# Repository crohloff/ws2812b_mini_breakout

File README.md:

# ws2812b-mini breakout
in-pcb placed ws2812b-mini

## dimensions
- 30mm x 25mm

## features
- 9 LEDs
- 3.3V - 5V level shifter
- in-pcb placed ws2812b-mini

## board front

## board back

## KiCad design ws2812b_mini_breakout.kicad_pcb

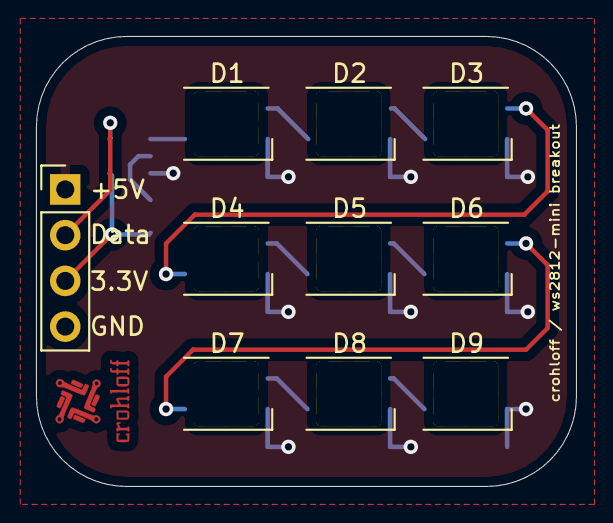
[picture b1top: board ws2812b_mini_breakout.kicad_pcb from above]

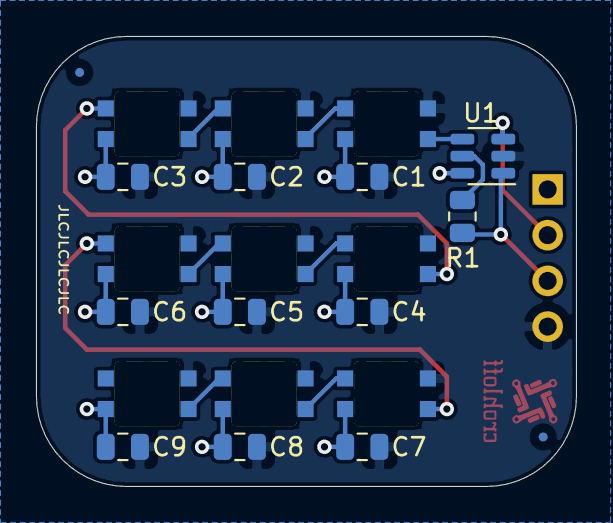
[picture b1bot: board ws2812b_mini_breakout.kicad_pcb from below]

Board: 2 copper layers, 30.0 x 25.0 mm, 21 parts (11 on the bottom side), 14 nets.

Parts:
C1, C2, C3, C4, C5, C6, C7, C8, C9: 100nF; C_0805_2012Metric
D1, D2, D3, D4, D5, D6, D7, D8, D9: WS2812B; ws2812_mini_inPCB
J1: Conn_01x04_Male; PinHeader_1x04_P2.54mm_Vertical
R1: 100k; R_0805_2012Metric
U1: SN74LVC1T45DBV; SOT-23-6

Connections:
+3V3: J1.3, R1.2, U1.1
+5V: C1.2, C2.2, C3.2, C4.2, C5.2, C6.2, C7.2, C8.2, C9.2, D1.1, D2.1, D3.1, D4.1, D5.1, D6.1, D7.1, D8.1, D9.1, J1.1, U1.6
/DATA_3.3V: J1.2, U1.3
/DATA_5V: D1.4, U1.4
GND: C1.1, C2.1, C3.1, C4.1, C5.1, C6.1, C7.1, C8.1, C9.1, D1.3, D2.3, D3.3, D4.3, D5.3, D6.3, D7.3, D8.3, D9.3, J1.4, U1.2
unnamed: D1.2, D2.4
unnamed: D2.2, D3.4
unnamed: D3.2, D4.4
unnamed: D4.2, D5.4
unnamed: D5.2, D6.4
unnamed: D6.2, D7.4
unnamed: D7.2, D8.4
unnamed: D8.2, D9.4
unnamed: R1.1, U1.5

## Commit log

2021-05-13 update files
